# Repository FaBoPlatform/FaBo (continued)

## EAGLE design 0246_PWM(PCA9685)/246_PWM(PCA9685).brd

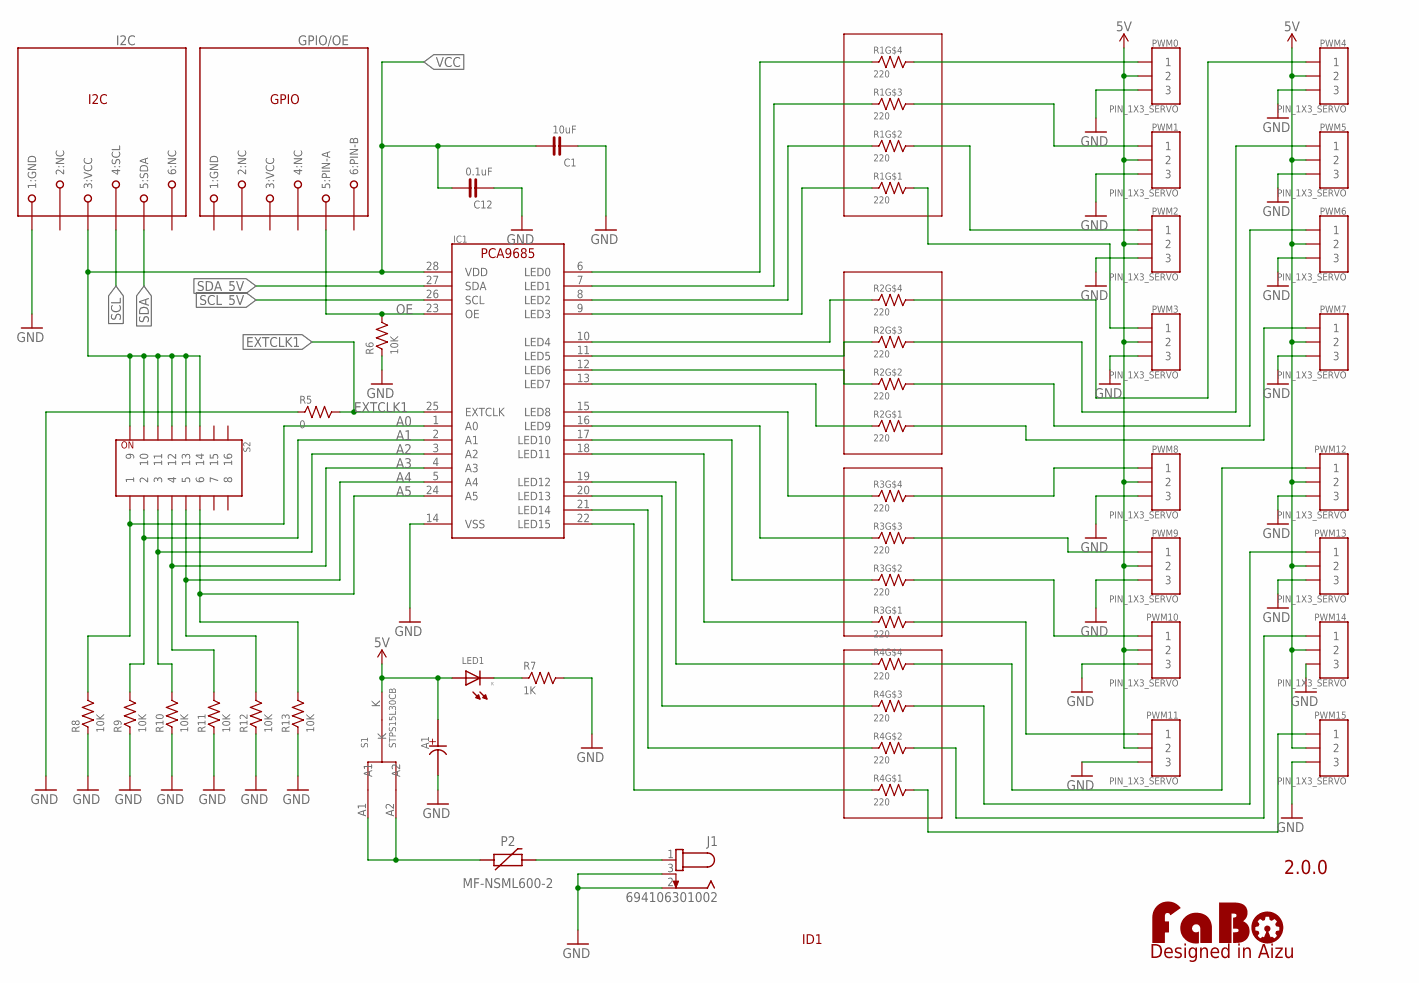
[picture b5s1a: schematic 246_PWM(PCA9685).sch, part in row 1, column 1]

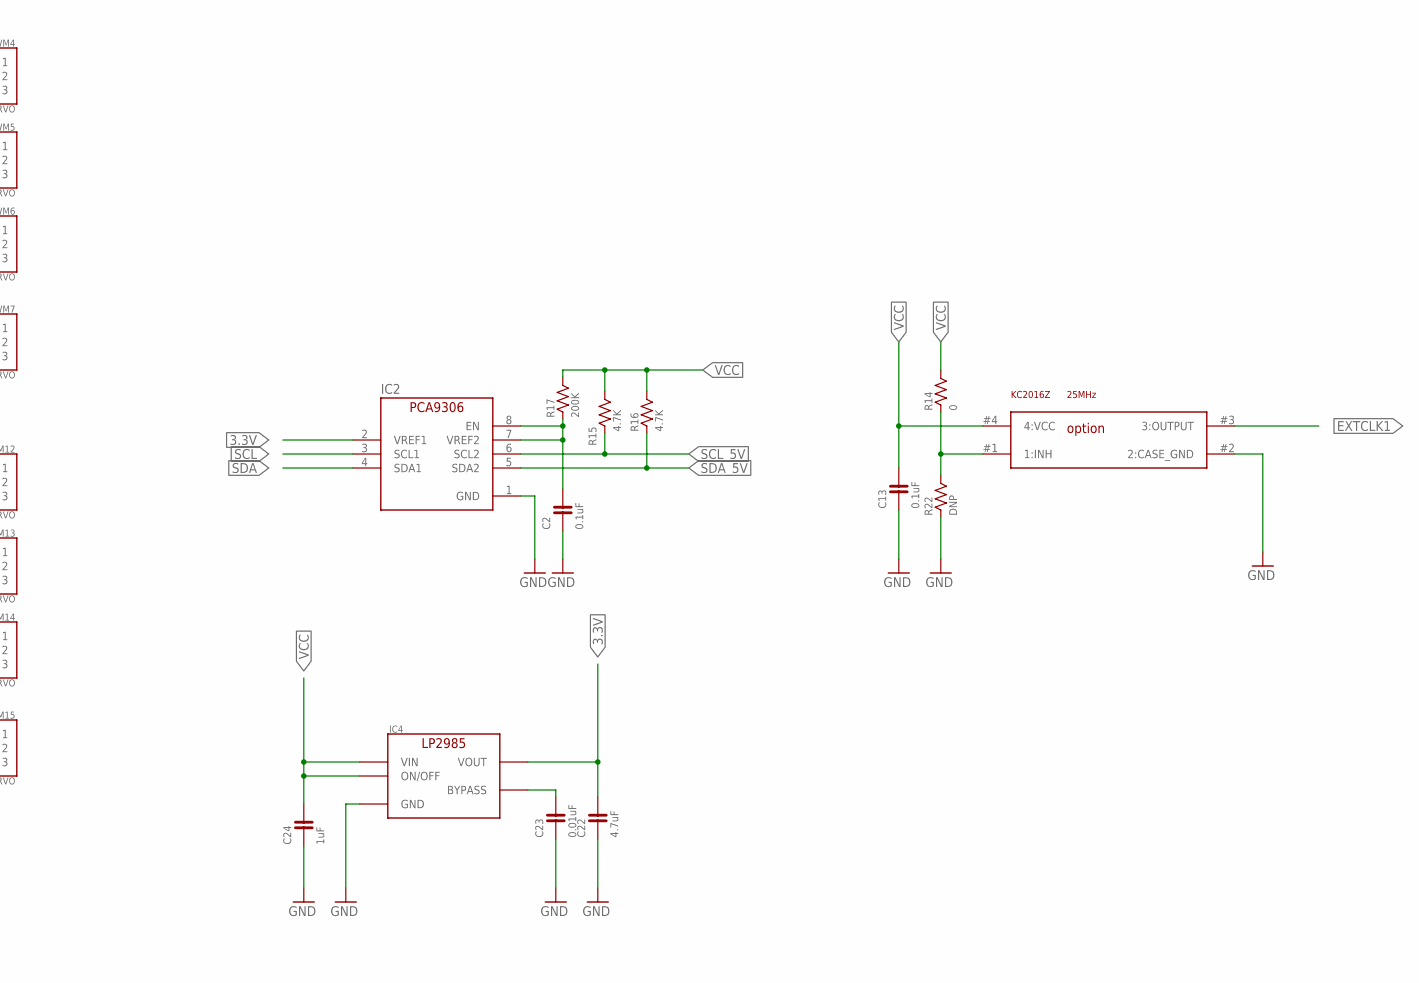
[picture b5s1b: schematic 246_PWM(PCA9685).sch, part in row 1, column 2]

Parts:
A1: CAPACITOR-OS-CON; F13
C1: 10uF; 0603
C2, C13: 0.1uF; 0402
C12: 0.1uF; 0603
C22: 4.7uF; 0603
C23: 0.01uF; 0603
C24: 1uF; 0603
GPIO/OE: MODULAR-JACK-6P-RJ11_GPIO; 7002-6PXC-X
I2C: MODULAR-JACK-6P-RJ11_I2C; 7002-6PXC-X
IC1: PCA9685BS; PCA9685
IC2: PCA9306_GM; XQFN8
IC4: LP2985-33DBV; SOT-23-5
J1: 694106301002
LED1: LED-0603; 0603
LOGO1: LOGO_FABO-M_BOTTOM; LOGO_FABO_M_BOTTOM
P2: MF-NSML600-2; 1206
PWM0, PWM1, PWM2, PWM3, PWM4, PWM5, PWM6, PWM7, PWM8, PWM9, PWM10, PWM11, PWM12, PWM13, PWM14, PWM15: PIN_1X3_SERVO; PIN_1X3_NOLABEL_PWM
R1, R2, R3, R4: 220; EXBV8V
R5: 0; 0603
R6, R8, R9, R10, R11, R12, R13: 10K; 0603
R7: 1K; 0603
R14: 0; 0402
R15, R16: 4.7K; 0402
R17: 200K; 0402
R22: DNP; 0402
S1: STPS15L30CB; STPS15L30C
S2: KHS82
U$11: KC2016Z

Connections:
1:GND: GPIO/OE.1 (1:GND)
3.3V: C22.2, IC2.2 (VREF1), IC4.5 (VOUT)
3:VCC: GPIO/OE.3 (3:VCC)
5V: A1.ANODE (+), LED1.ANODE, PWM0.2:VCC (2), PWM1.2:VCC (2), PWM2.2:VCC (2), PWM3.2:VCC (2), PWM4.2:VCC (2), PWM5.2:VCC (2), PWM6.2:VCC (2), PWM7.2:VCC (2), PWM8.2:VCC (2), PWM9.2:VCC (2), PWM10.2:VCC (2), PWM11.2:VCC (2), PWM12.2:VCC (2), PWM13.2:VCC (2), PWM14.2:VCC (2), PWM15.2:VCC (2), S1.K
A0: IC1.1 (A0), R8.2, S2.1
A1: IC1.2 (A1), R9.2, S2.2
A2: IC1.3 (A2), R10.2, S2.3
A3: IC1.4 (A3), R11.2, S2.4
A4: IC1.5 (A4), R12.2, S2.5
A5: IC1.24 (A5), R13.2, S2.6
EXTCLK1: IC1.25 (EXTCLK), R5.2, U$11.#3 (3:OUTPUT)
GND: A1.CATHODE (-), C1.1, C2.P$1 (1), C12.1, C13.P$1 (1), C22.1, C23.1, C24.1, I2C.1 (1:GND), IC1.14 (VSS), IC2.1 (GND), IC4.2 (GND), J1.2, J1.3, PWM0.3:GND (3), PWM1.3:GND (3), PWM2.3:GND (3), PWM3.3:GND (3), PWM4.3:GND (3), PWM5.3:GND (3), PWM6.3:GND (3), PWM7.3:GND (3), PWM8.3:GND (3), PWM9.3:GND (3), PWM10.3:GND (3), PWM11.3:GND (3), PWM12.3:GND (3), PWM13.3:GND (3), PWM14.3:GND (3), PWM15.3:GND (3), R5.1, R6.1, R7.2, R8.1, R9.1, R10.1, R11.1, R12.1, R13.1, R22.P$1 (1), U$11.#2 (2:CASE_GND)
unnamed: IC1.6 (LED0), R1.4 (1)
unnamed: IC1.7 (LED1), R1.3 (1)
unnamed: IC1.8 (LED2), R1.2 (1)
unnamed: IC1.9 (LED3), R1.1
unnamed: PWM0.1:SIGNAL (1), R1.5 (2)
unnamed: PWM1.1:SIGNAL (1), R1.6 (2)
unnamed: PWM2.1:SIGNAL (1), R1.7 (2)
unnamed: PWM3.1:SIGNAL (1), R1.8 (2)
unnamed: IC1.10 (LED4), R2.4 (1)
unnamed: IC1.11 (LED5), R2.3 (1)
unnamed: IC1.12 (LED6), R2.2 (1)
unnamed: IC1.13 (LED7), R2.1
unnamed: IC1.15 (LED8), R3.4 (1)
unnamed: IC1.16 (LED9), R3.3 (1)
unnamed: IC1.17 (LED10), R3.2 (1)
unnamed: IC1.18 (LED11), R3.1
unnamed: IC1.19 (LED12), R4.4 (1)
unnamed: IC1.20 (LED13), R4.3 (1)
unnamed: IC1.21 (LED14), R4.2 (1)
unnamed: IC1.22 (LED15), R4.1
unnamed: PWM4.1:SIGNAL (1), R2.5 (2)
unnamed: PWM5.1:SIGNAL (1), R2.6 (2)
unnamed: PWM6.1:SIGNAL (1), R2.7 (2)
unnamed: PWM7.1:SIGNAL (1), R2.8 (2)
unnamed: PWM8.1:SIGNAL (1), R3.5 (2)
unnamed: PWM9.1:SIGNAL (1), R3.6 (2)
unnamed: PWM10.1:SIGNAL (1), R3.7 (2)
unnamed: PWM11.1:SIGNAL (1), R3.8 (2)
unnamed: PWM12.1:SIGNAL (1), R4.5 (2)
unnamed: PWM13.1:SIGNAL (1), R4.6 (2)
unnamed: PWM14.1:SIGNAL (1), R4.7 (2)
unnamed: PWM15.1:SIGNAL (1), R4.8 (2)
unnamed: P2.P$1 (1), S1.A1, S1.A2
unnamed: C23.2, IC4.4 (BYPASS)
unnamed: LED1.CATHODE, R7.1
unnamed: R14.P$1 (1), R22.P$2 (2), U$11.#1 (1:INH)
OE: GPIO/OE.5 (5:PIN-A), IC1.23 (OE), R6.2
PTCP1: J1.1, P2.P$2 (2)
SCL: I2C.4 (4:SCL), IC2.3 (SCL1)
SCL_5V: IC1.26 (SCL), IC2.6 (SCL2), R15.P$1 (1)
SDA: I2C.5 (5:SDA), IC2.4 (SDA1)
SDA_5V: IC1.27 (SDA), IC2.5 (SDA2), R16.P$1 (1)
VCC: C1.2, C12.2, C13.P$2 (2), C24.2, I2C.3 (3:VCC), IC1.28 (VDD), IC4.1 (VIN), IC4.3 (ON/OFF), R14.P$2 (2), R15.P$2 (2), R16.P$2 (2), R17.P$2 (2), S2.9, S2.10, S2.11, S2.12, S2.13, S2.14, U$11.#4 (4:VCC)
VCC_EN: C2.P$2 (2), IC2.7 (VREF2), IC2.8 (EN), R17.P$1 (1)

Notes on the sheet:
2.0.0
ID1
option

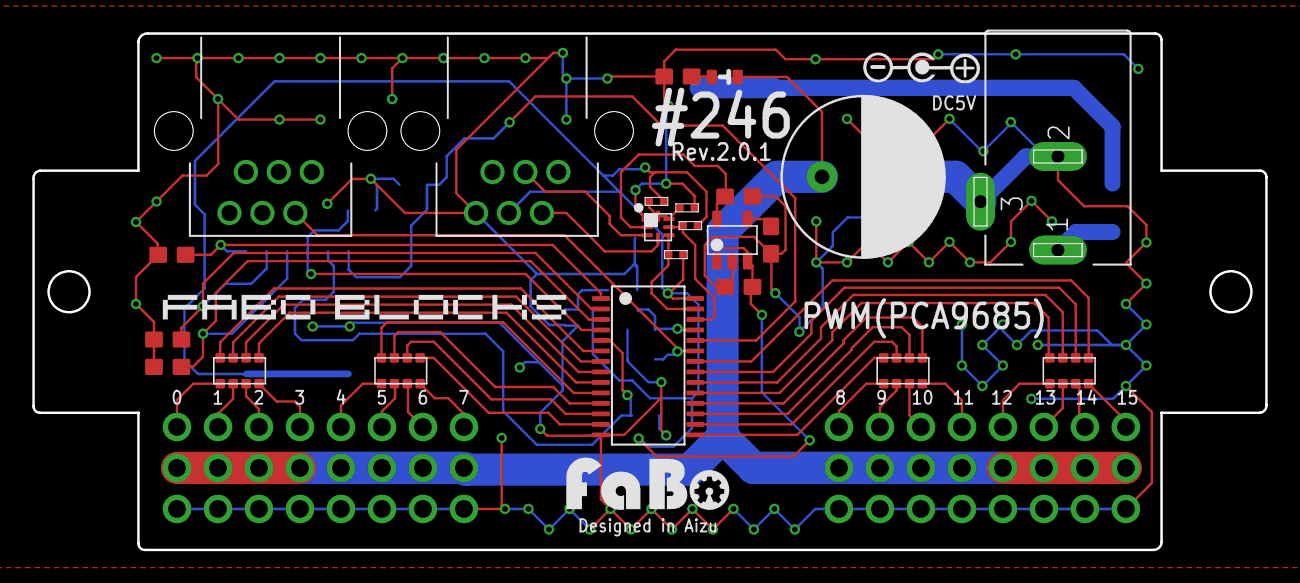
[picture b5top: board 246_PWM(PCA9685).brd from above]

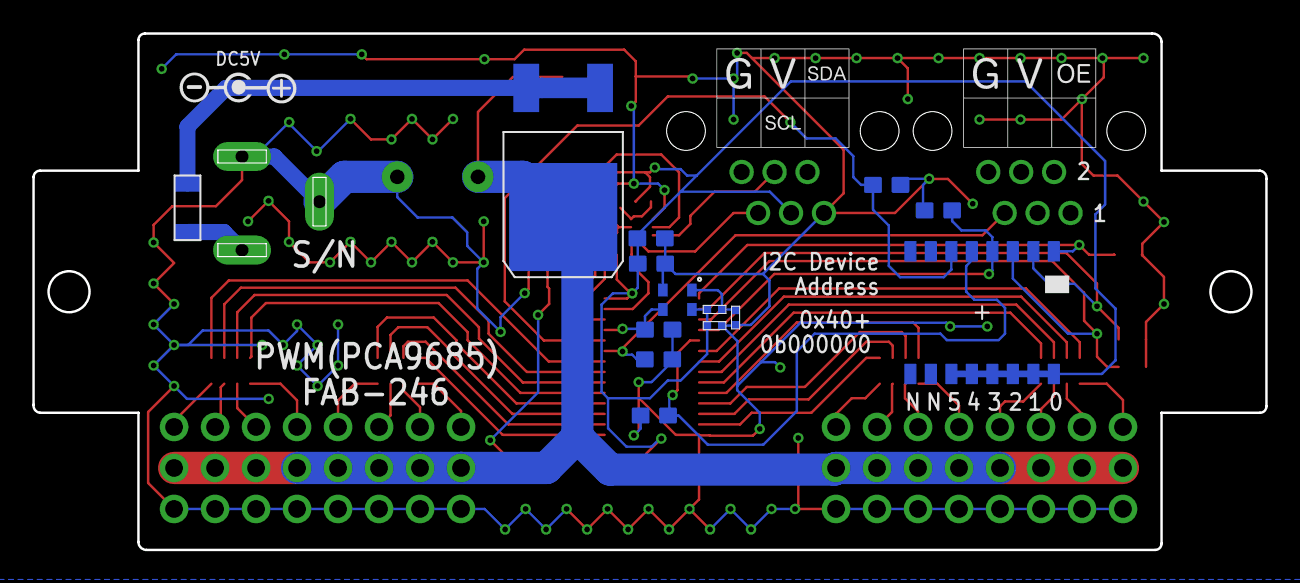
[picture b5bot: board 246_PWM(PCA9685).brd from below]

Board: 2 copper layers, 76.4 x 32.0 mm, 56 parts (15 on the bottom side), 54 nets.

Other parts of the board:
U$2, U$4: 4-1BLOCK

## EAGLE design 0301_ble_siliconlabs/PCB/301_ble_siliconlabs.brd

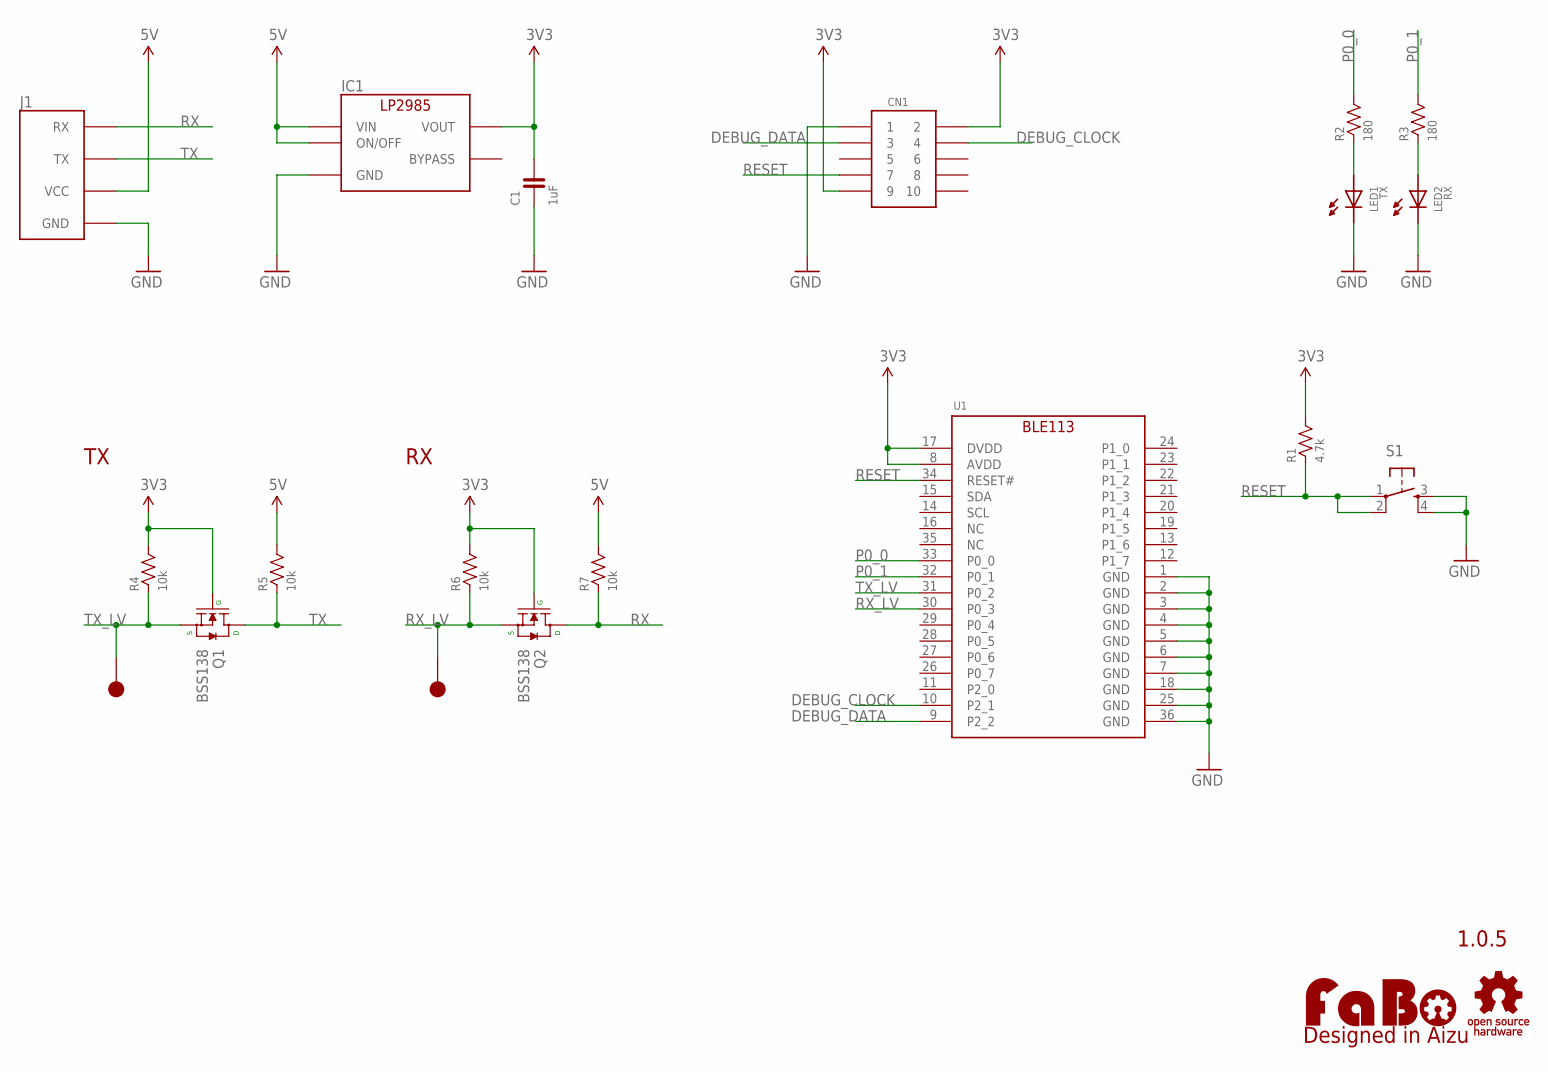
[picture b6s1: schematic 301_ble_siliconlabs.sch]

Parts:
C1: 1uF; 0603-NARROW
CN1: PIN-HEADER-SMT(1.27MM)2X5
IC1: LP2985-33DBV; SOT-23-5
J1: FABO_BRICK_SERIAL
LED1: TX; 0603
LED2: RX; 0603
LOGO1: LOGO_FABO-M_BOTTOM; LOGO_FABO_M_BOTTOM
Q1, Q2: BSS138; SOT23-3
R1: 4.7k; 0603-NARROW
R2, R3: 180; 0603
R4, R5, R6, R7: 10k; 0603-NARROW
S1: TACT-SWITCH-SMD_KMR2; KMR2
TP10, TP11: TP-15
U1: BLUEGIGA-BLE113
U$2: LOGO_OSHW-M_BOTTOM; LOGO_OSHW_M_BOTTOM

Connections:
3V3: C1.2, CN1.2, CN1.9, IC1.5 (VOUT), Q1.1 (G), Q2.1 (G), R1.2, R4.2, R6.2, U1.8 (AVDD), U1.17 (DVDD)
5V: IC1.1 (VIN), IC1.3 (ON/OFF), J1.VCC, R5.2, R7.2
DEBUG_CLOCK: CN1.4, U1.10 (P2_1)
DEBUG_DATA: CN1.3, U1.9 (P2_2)
GND: C1.1, CN1.1, IC1.2 (GND), J1.GND, LED1.CATHODE, LED2.CATHODE, S1.3, S1.4, U1.1 (GND), U1.2 (GND), U1.3 (GND), U1.4 (GND), U1.5 (GND), U1.6 (GND), U1.7 (GND), U1.18 (GND), U1.25 (GND), U1.36 (GND)
unnamed: LED1.ANODE, R2.1
unnamed: LED2.ANODE, R3.1
P0_0: R2.2, U1.33 (P0_0)
P0_1: R3.2, U1.32 (P0_1)
RESET: CN1.7, R1.1, S1.1, S1.2, U1.34 (RESET#)
RX: J1.RX, Q2.3 (D), R7.1
RX_LV: Q2.2 (S), R6.1, TP10.1, U1.30 (P0_3)
TX: J1.TX, Q1.3 (D), R5.1
TX_LV: Q1.2 (S), R4.1, TP11.1, U1.31 (P0_2)

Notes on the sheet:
1.0.5

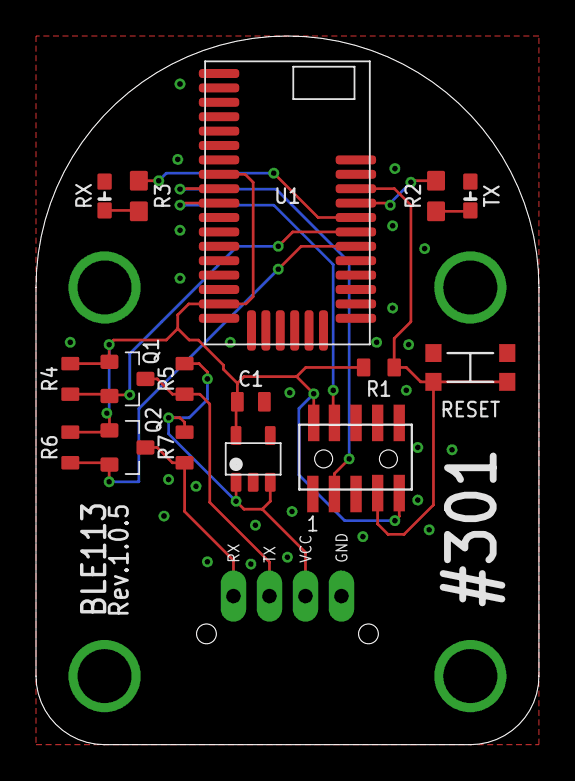
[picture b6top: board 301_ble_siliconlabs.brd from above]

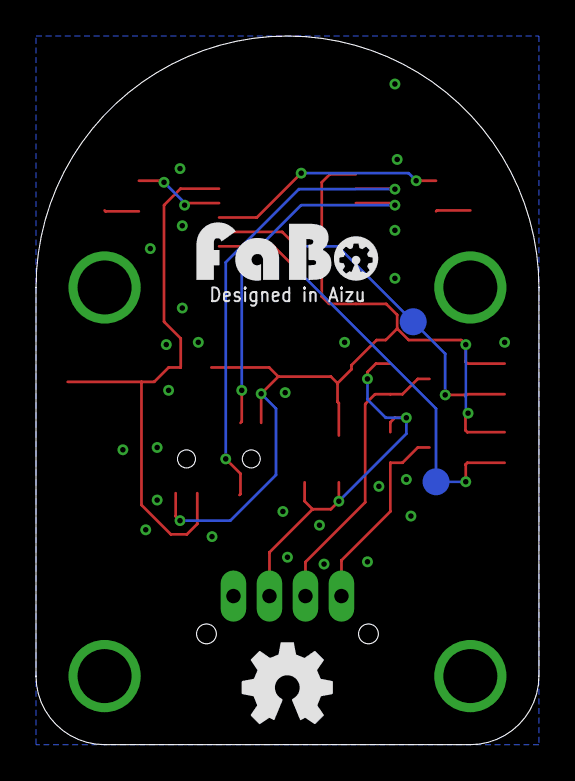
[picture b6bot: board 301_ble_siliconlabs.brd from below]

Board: 2 copper layers, 27.9 x 39.4 mm, 21 parts (2 on the bottom side), 14 nets.

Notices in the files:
parts and their libraries:
FaBo-Block: Released under the Creative Commons Attribution-ShareAlike 4.0 License
https://creativecommons.org/licenses/by-sa/4.0
FaBo-etc: Released under the Creative Commons
